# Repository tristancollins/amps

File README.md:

# Amps
## Generic Boards
- General MOSFET breakout
- General TO220 breakout

I've moved my amp pcbs to their own repos.
- Guitar Pre-amp
- Guitar Phase Inverter (LTPI)
- Guitar Valve-driven effects loop
- Guitar Power Supply
- Guitar Bone Ray Tone Stack
- Guitar Solid State effects loop
- Guitar Solid State Reverb
- Guitar Input PCB - UNTESTED - for my specific builds
- Guitar Cathodyne Phase Inverter - UNTESTED

In action: https://www.tristancollins.me/ax84/Mutineer/Built/IMG_0032.jpg
https://www.tristancollins.me/ax84/Mutineer/Built/IMG_0031.jpg

- HiFi PCL82 SE board
- HiFi Maida Regulator
- HiFi 5V supply and mains relay
- HiFi Baxandall Preamp

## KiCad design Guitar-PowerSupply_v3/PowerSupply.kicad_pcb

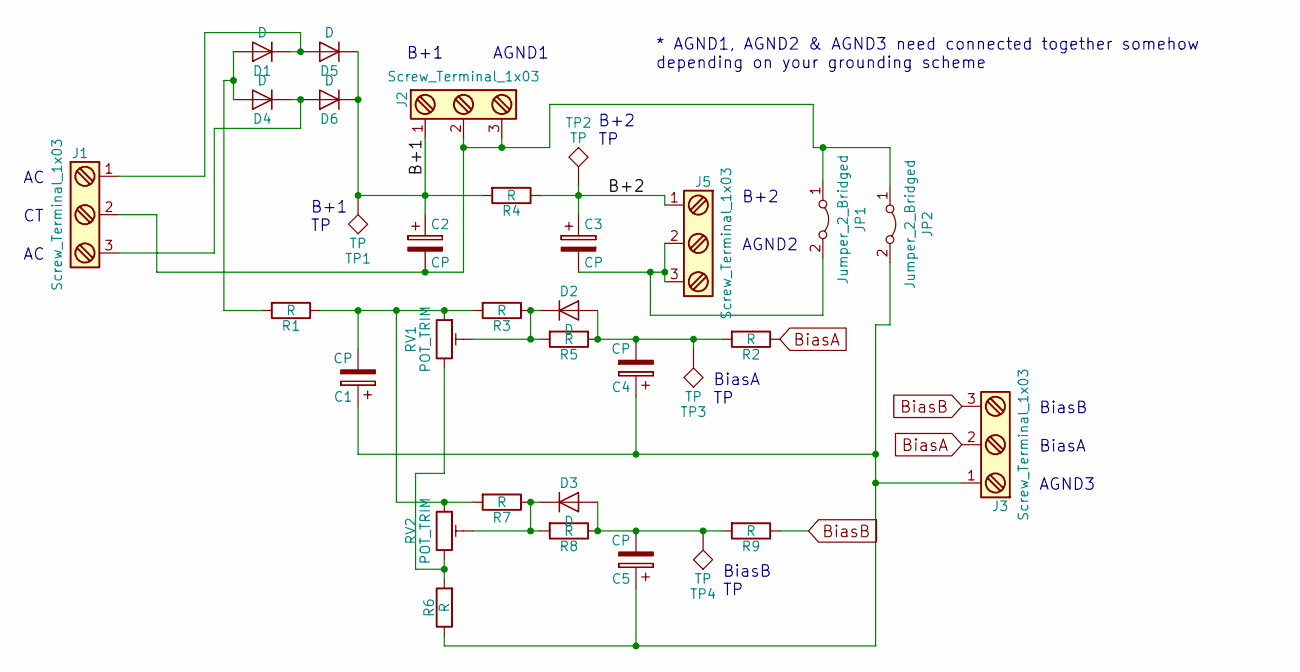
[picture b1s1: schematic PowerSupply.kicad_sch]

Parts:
C1, C4, C5: CP; CP_Radial_D10.0mm_P2.50mm_P5.00mm; MPN UPW2C100MPD
C2, C3: CP; CP_Radial_D18.0mm_P7.50mm
D1, D2, D3, D4, D5, D6: D; Diode_DO-41_SOD81_Horizontal_RM10
J1, J2, J3, J5: Screw_Terminal_1x03; PhoenixContact_MCV-G_03x5.08mm_Vertical; MPN 1729131
JP1, JP2: Jumper_2_Bridged; SolderJumper-2_P1.3mm_Bridged_RoundedPad1.0x1.5mm
R1: R; R_Axial_DIN0516_L15.5mm_D5.0mm_P20.32mm_Horizontal
R2, R3, R5, R6, R7, R8, R9: R; R_Axial_DIN0309_L9.0mm_D3.2mm_P12.70mm_Horizontal
R4: R; R_Axial_Power_L48.0mm_W12.5mm_P55.88mm
RV1, RV2: POT_TRIM; Potentiometer_Trimmer_Bourns_3339S_Vertical; MPN 3386P-1-103TLF
TP1, TP2, TP3, TP4: TP; Test_Point_Keystone_5005-5009_Compact

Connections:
/B+1: C2.1, D5.1 (K), D6.1 (K), J2.1, R4.2, TP1.1
/B+2: C3.1, J5.1, R4.1, TP2.1
BiasA: J3.2, R2.1
BiasB: J3.3, R9.1
unnamed: C1.1, C4.1, C5.1, J3.1, JP2.2 (B), R6.1
unnamed: C1.2, R1.1, R3.2, R7.2, RV1.1, RV2.1
unnamed: C2.2, J1.2, J2.2, J2.3, JP1.1 (A), JP2.1 (A)
unnamed: C3.2, J5.2, J5.3, JP1.2 (B)
unnamed: C4.2, D2.2 (A), R2.2, R5.1, TP3.1
unnamed: C5.2, D3.2 (A), R8.1, R9.2, TP4.1
unnamed: D1.1 (K), D5.2 (A), J1.1
unnamed: D1.2 (A), D4.2 (A), R1.2
unnamed: D2.1 (K), R3.1, R5.2, RV1.2
unnamed: D3.1 (K), R7.1, R8.2, RV2.2
unnamed: D4.1 (K), D6.2 (A), J1.3
unnamed: R6.2, RV1.3, RV2.3

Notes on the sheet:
B+2 TP
B+1 TP
BiasB
BiasA TP
* AGND1, AGND2 & AGND3 need connected together somehow depending on your grounding scheme
AGND2
B+2
BiasB TP
B+1
BiasA
AGND1
AGND3

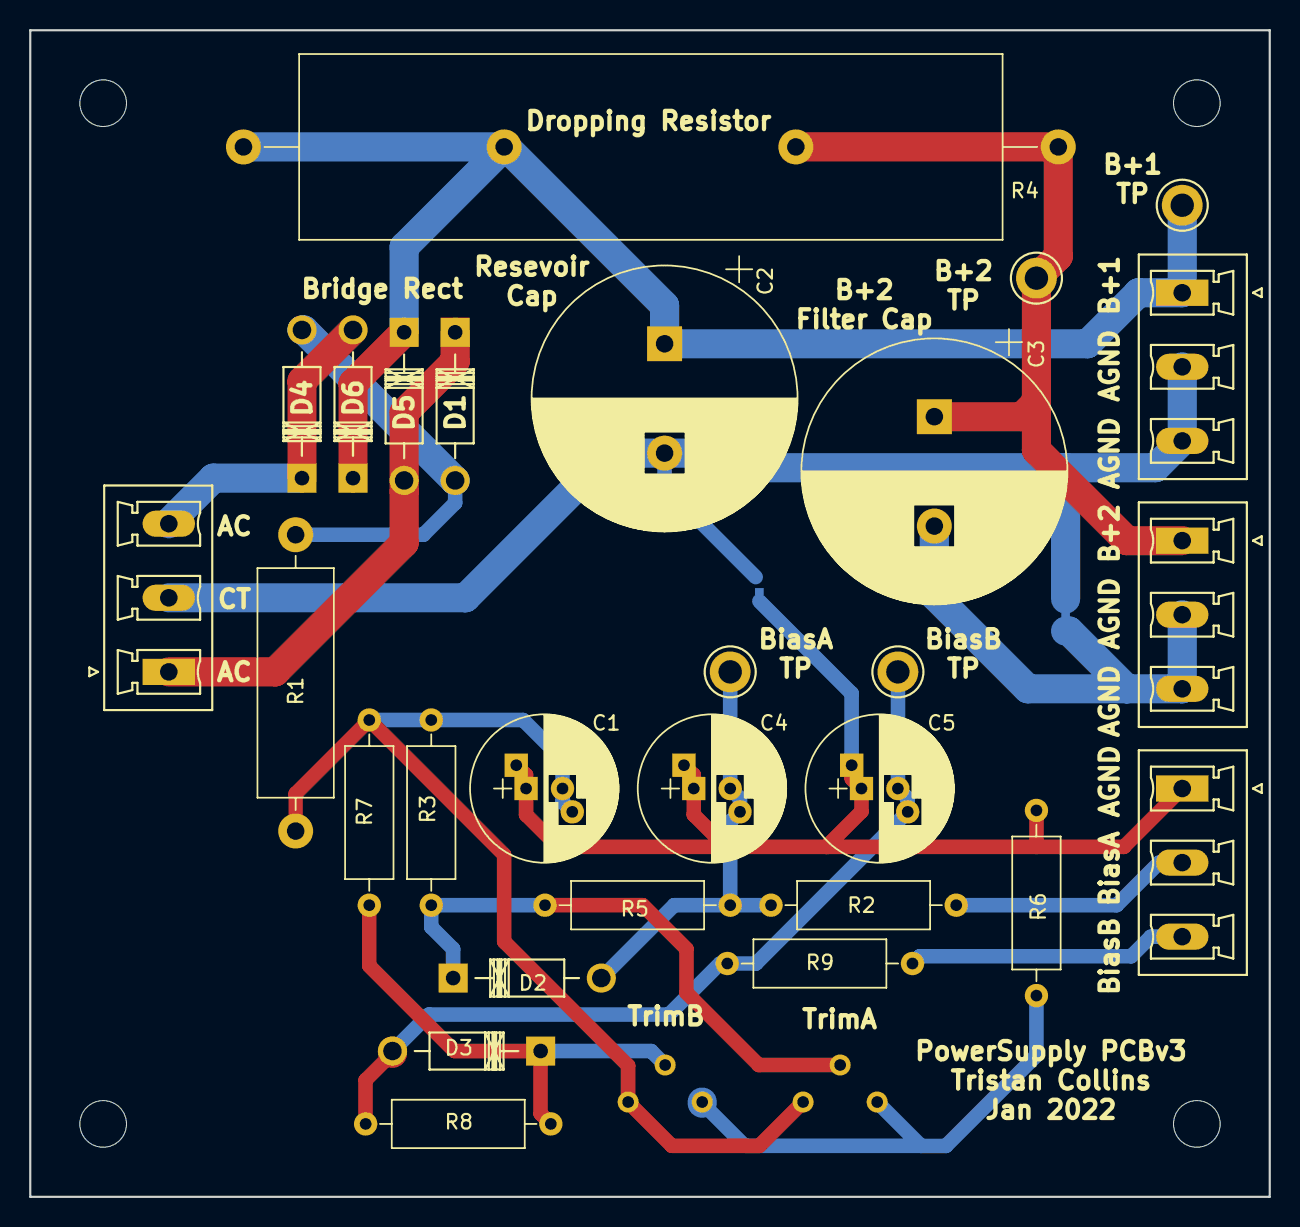
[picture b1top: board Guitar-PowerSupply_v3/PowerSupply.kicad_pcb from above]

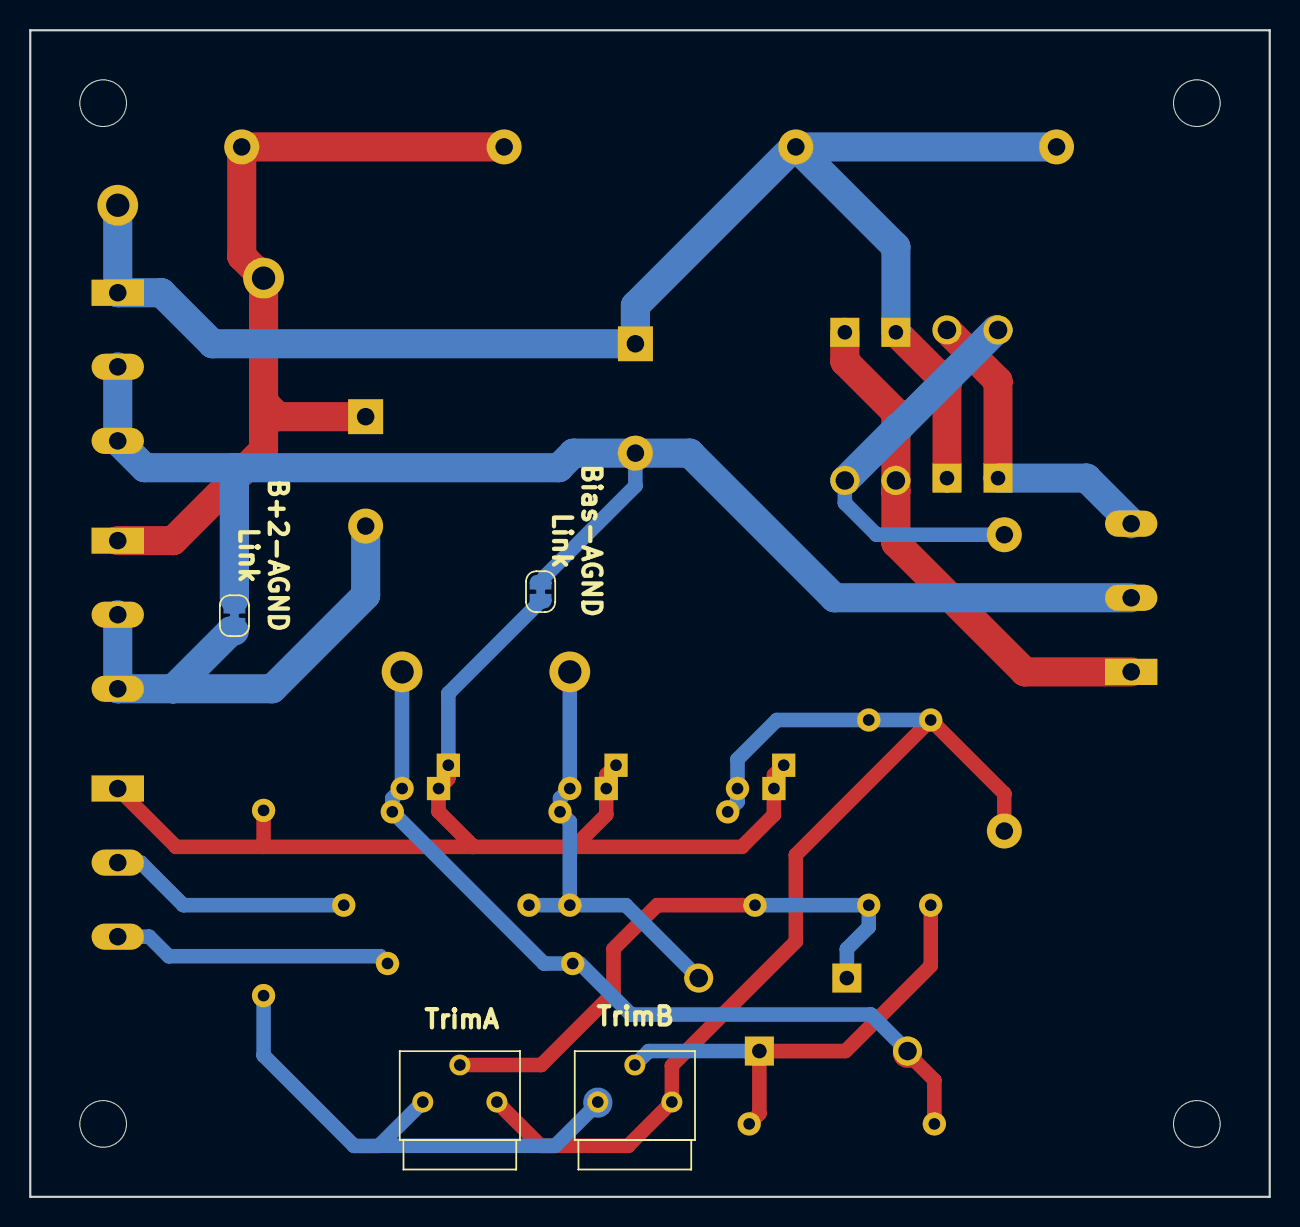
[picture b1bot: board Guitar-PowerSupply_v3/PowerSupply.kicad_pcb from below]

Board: 2 copper layers, 85.0 x 80.0 mm, 32 parts (4 on the bottom side), 16 nets.

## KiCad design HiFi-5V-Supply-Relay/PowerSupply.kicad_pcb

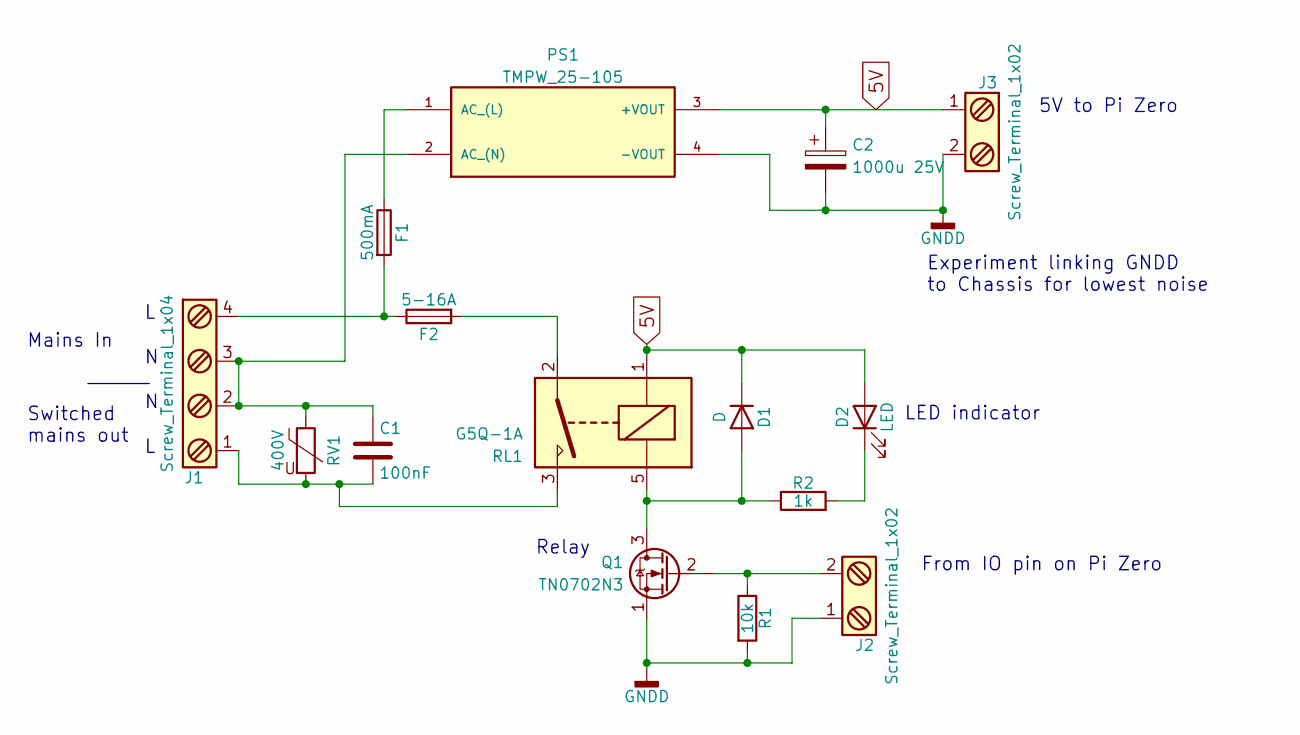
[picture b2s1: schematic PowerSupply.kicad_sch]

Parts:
C1: 100nF; C_Rect_L18.0mm_W5.0mm_P15.00mm_FKS3_FKP3; mpn 80-R71PI3100JE3EK
C2: 1000u 25V; CP_Radial_D10.0mm_P5.00mm
D1: D; D_DO-41_SOD81_P3.81mm_Vertical_KathodeUp
D2: LED; PinHeader_1x02_P2.54mm_Vertical
F1: 500mA; Fuseholder_Cylinder-5x20mm_Bulgin_FX0456_Vertical_Closed; mpn FX0456
F2: 5-16A; Fuseholder_Cylinder-5x20mm_Bulgin_FX0456_Vertical_Closed; mpn FX0456
J1: Screw_Terminal_1x04; TerminalBlock_Phoenix_PT-1,5-4-5.0-H_1x04_P5.00mm_Horizontal
J2, J3: Screw_Terminal_1x02; TerminalBlock_Phoenix_PT-1,5-2-3.5-H_1x02_P3.50mm_Horizontal
PS1: TMPW_25-105; CONV_TMPW_25-105; PARTREV April 20,2021
Q1: TN0702N3; TO-92_HandSolder; mpn TN0702N3-G
R1: 10k; R_Axial_DIN0207_L6.3mm_D2.5mm_P2.54mm_Vertical
R2: 1k; R_Axial_DIN0207_L6.3mm_D2.5mm_P2.54mm_Vertical
RL1: G5Q-1A; Relay_SPST_Omron-G5Q-1A; mpn G5Q-1A4-EU DC5
RV1: 400V; RV_Disc_D7mm_W5.1mm_P5mm; mpn 495-3785-ND

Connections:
5V: C2.1, D1.1 (K), D2.2 (A), J3.1, PS1.3 (+VOUT), RL1.1
GNDD: C2.2, J2.1, J3.2, PS1.4 (-VOUT), Q1.1 (S), R1.2
unnamed: C1.1, J1.2, J1.3, PS1.2 (AC_(N)), RV1.1
unnamed: C1.2, J1.1, RL1.3, RV1.2
unnamed: D1.2 (A), Q1.3 (D), R2.1, RL1.5
unnamed: D2.1 (K), R2.2
unnamed: F1.1, PS1.1 (AC_(L))
unnamed: F1.2, F2.1, J1.4
unnamed: F2.2, RL1.2
unnamed: J2.2, Q1.2 (G), R1.1

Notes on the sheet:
From IO pin on Pi Zero
Mains In
Relay
LED indicator
Switched mains out
Experiment linking GNDD to Chassis for lowest noise
5V to Pi Zero

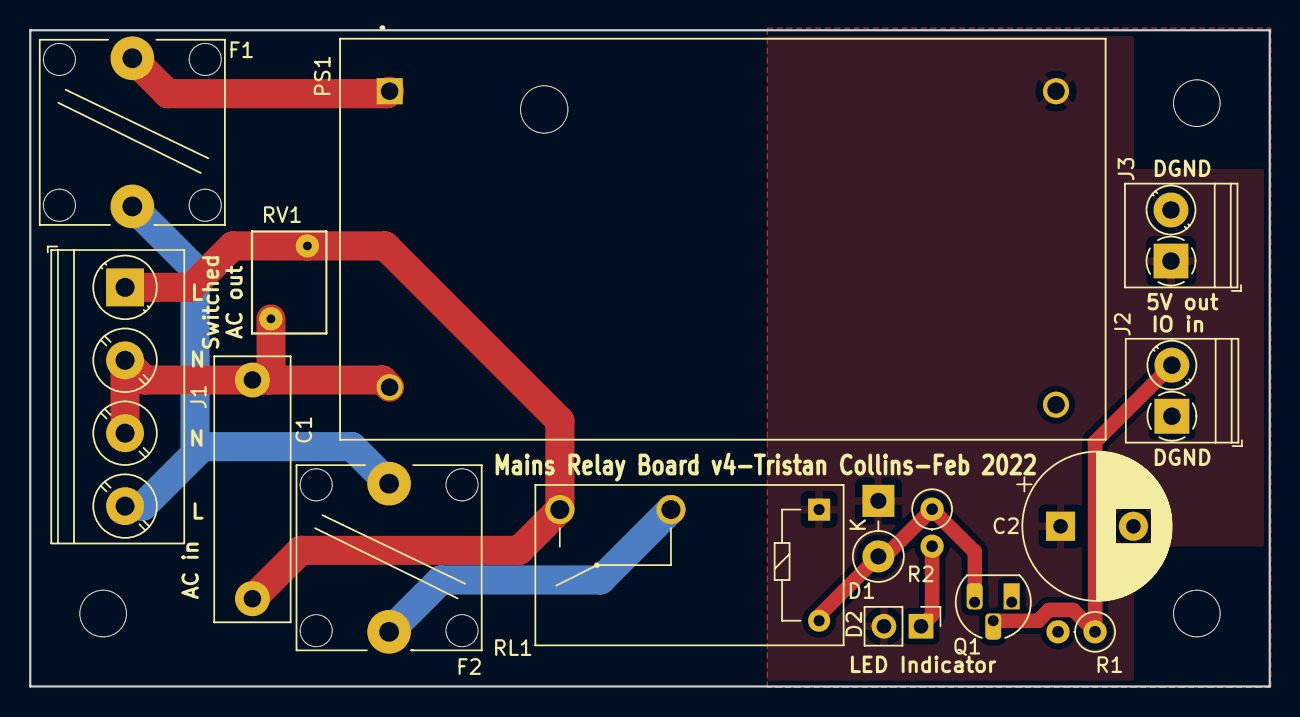
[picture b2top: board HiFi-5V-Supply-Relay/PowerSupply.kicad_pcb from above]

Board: 2 copper layers, 85.0 x 45.0 mm, 15 parts (0 on the bottom side), 10 nets.

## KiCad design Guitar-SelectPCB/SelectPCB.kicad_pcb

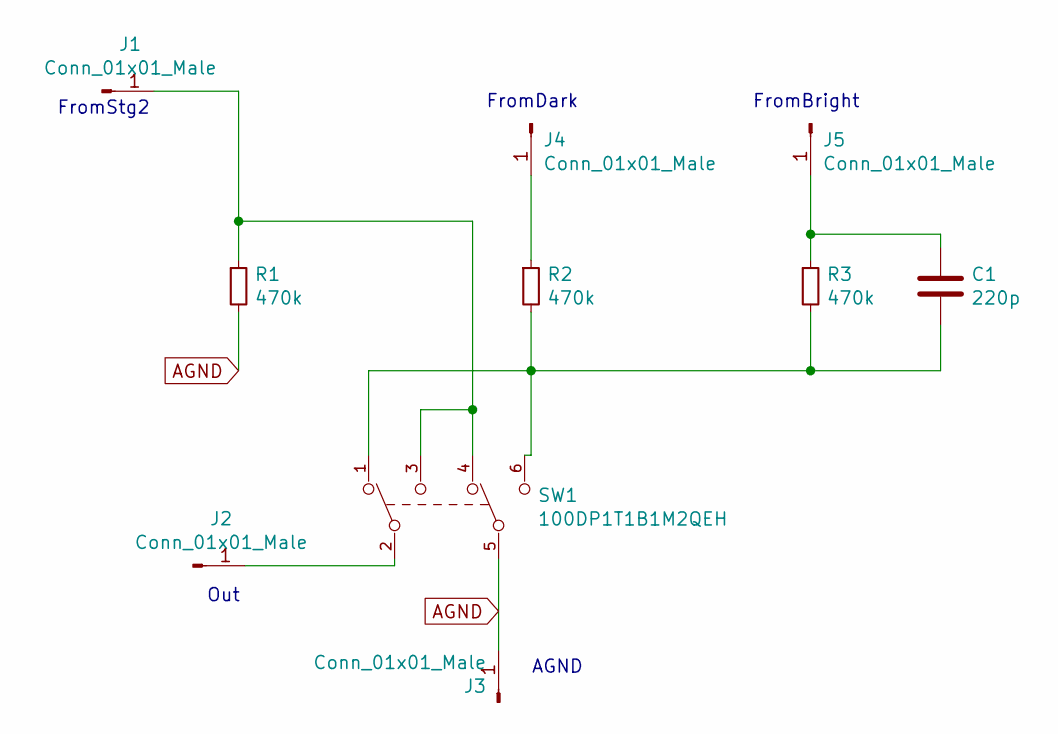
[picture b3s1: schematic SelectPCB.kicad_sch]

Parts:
C1: 220p; C_Disc_D7.5mm_W5.0mm_P7.50mm
J1, J2, J3, J4, J5: Conn_01x01_Male; SolderWirePad_1x01_Drill1.5mm
R1, R2, R3: 470k; R_Axial_DIN0207_L6.3mm_D2.5mm_P10.16mm_Horizontal
SW1: 100DP1T1B1M2QEH; E-Switch-100DP1T1B1M2QEH-0; Current Rating 5A (AC/DC); Voltage Rating - AC 120V; mouser part number 612-100-F1121; digikey description Toggle Switch DPDT Panel Mount

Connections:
AGND: J3.1, R1.2, SW1.5
unnamed: C1.1, J5.1, R3.1
unnamed: C1.2, R2.2, R3.2, SW1.1, SW1.6
unnamed: J1.1, R1.1, SW1.3, SW1.4
unnamed: J2.1, SW1.2
unnamed: J4.1, R2.1

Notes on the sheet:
Out
FromBright
FromDark
AGND
FromStg2

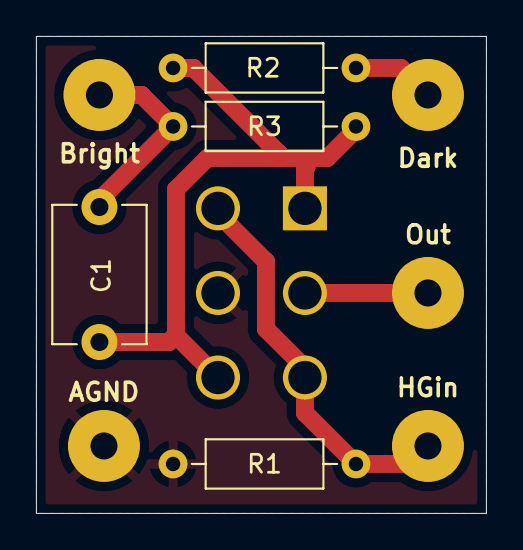
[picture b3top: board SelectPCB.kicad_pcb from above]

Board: 2 copper layers, 25.0 x 26.5 mm, 10 parts (1 on the bottom side), 6 nets.

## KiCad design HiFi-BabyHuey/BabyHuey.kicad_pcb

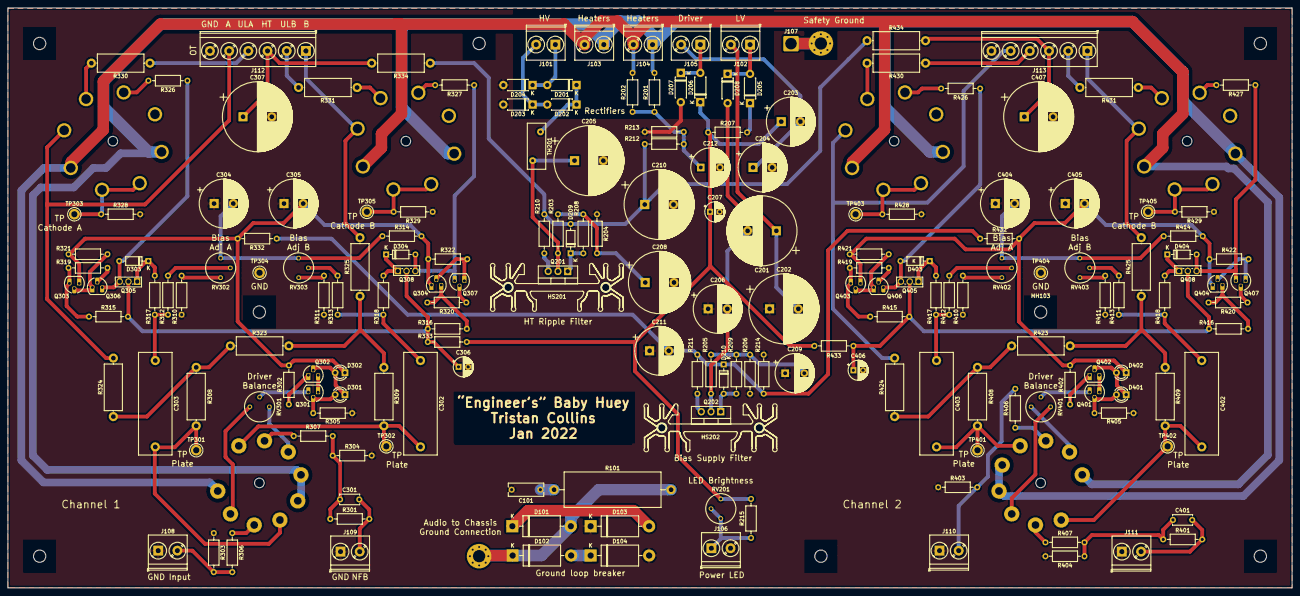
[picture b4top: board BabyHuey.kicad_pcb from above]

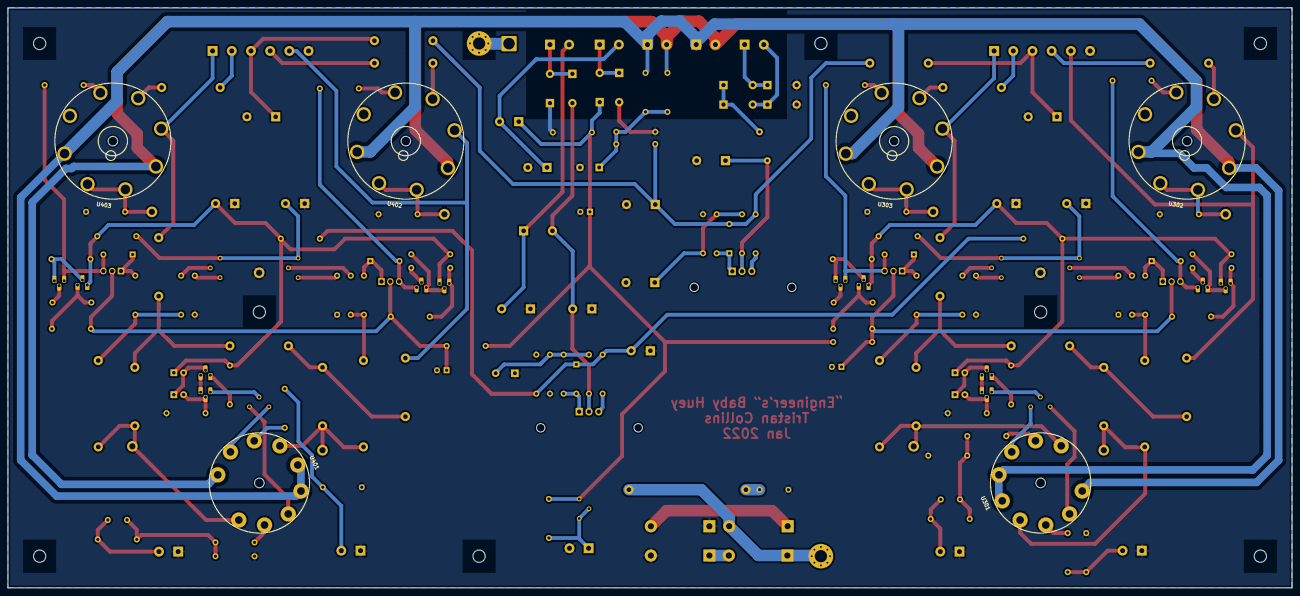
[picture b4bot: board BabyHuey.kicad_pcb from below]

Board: 2 copper layers, 334.5 x 151.1 mm, 200 parts (6 on the bottom side), 120 nets.

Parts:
C101: 100n; C_Rect_L9.0mm_W3.2mm_P7.50mm_MKT
C201, C202: 470u 100V; CP_Radial_D18.0mm_P7.50mm
C203, C204: 2200u 25V; CP_Radial_D12.5mm_P5.00mm
C205, C210, C307, C407: 47u 450V; CP_Radial_D18.0mm_P7.50mm
C206, C211, C304, C305, C404, C405: 47u 160V; CP_Radial_D12.5mm_P5.00mm
C207, C306, C406: 47u 25V; CP_Radial_D5.0mm_P2.50mm
C208: 10u 450V; CP_Radial_D16.0mm_P7.50mm
C209: 10u 160V; CP_Radial_D10.0mm_P5.00mm
C212: 10u 200V; CP_Radial_D10.0mm_P5.00mm
C301, C401: DNP; C_Disc_D5.0mm_W2.5mm_P5.00mm
C302, C303, C402, C403: 220n 630V; C_Rect_L26.5mm_W8.5mm_P22.50mm_MKS4
D101, D102, D103, D104: SF51-B; D_DO-201AD_P15.24mm_Horizontal
D201, D202, D203, D204, D205, D206, D207, D208: UF4007; D_DO-41_SOD81_P7.62mm_Horizontal
D209, D210, D303, D304, D403, D404: BZX79C10; D_DO-35_SOD27_P7.62mm_Horizontal
D301, D302, D401, D402: Red; LED_D3.0mm
HS201, HS202: HSE-B20250-040H
J101, J102, J103, J104, J105, J106, J108, J109, J110, J111: Screw_Terminal_01x02; TerminalBlock_Phoenix_PT-1,5-2-5.0-H_1x02_P5.00mm_Horizontal
J107: Conn_01x01_Female; SolderWire-2.5sqmm_1x01_D2.4mm_OD3.6mm
J112, J113: Screw_Terminal_01x06; TerminalBlock_Phoenix_PT-1,5-6-5.0-H_1x06_P5.00mm_Horizontal
MH101, MH102, MH103, MH104, MH105, MH106, MH107, MH108: MountingHole; MountingHole_3.2mm_M3
MH109, MH110: MountingHole_Pad; MountingHole_3.2mm_M3_Pad_Via
Q201: FQPF8N60C; TO-220-3_Vertical
Q202: FQPF7P20; TO-220-3_Vertical
Q301, Q302, Q303, Q304, Q306, Q307, Q401, Q402, Q403, Q404, Q406, Q407: 2n5551; TO-92_HandSolder
Q305, Q308, Q405, Q408: STU9HN65M2; TO-251-3_Vertical
R101: 10r 5W; R_Axial_Power_L25.0mm_W9.0mm_P30.48mm
R201, R202, R208, R209, R317, R318, R319, R320, R417, R418, R419, R420: 100r; R_Axial_DIN0207_L6.3mm_D2.5mm_P10.16mm_Horizontal
R203, R205, R314, R414: 22k; R_Axial_DIN0207_L6.3mm_D2.5mm_P10.16mm_Horizontal
R204, R206, R312, R313, R412, R413: 1Meg; R_Axial_DIN0207_L6.3mm_D2.5mm_P10.16mm_Horizontal
R207, R212, R214: 330k; R_Axial_DIN0207_L6.3mm_D2.5mm_P10.16mm_Horizontal
R210: 22r; R_Axial_DIN0207_L6.3mm_D2.5mm_P10.16mm_Horizontal
R211: 10r; R_Axial_DIN0207_L6.3mm_D2.5mm_P10.16mm_Horizontal
R213, R305, R405: 47k; R_Axial_DIN0207_L6.3mm_D2.5mm_P10.16mm_Horizontal
R215: TBD; R_Axial_DIN0207_L6.3mm_D2.5mm_P10.16mm_Horizontal
R301, R401: DNP; R_Axial_DIN0207_L6.3mm_D2.5mm_P10.16mm_Horizontal
R302, R402: 680r; R_Axial_DIN0207_L6.3mm_D2.5mm_P10.16mm_Horizontal
R303, R403: 100k; R_Axial_DIN0207_L6.3mm_D2.5mm_P10.16mm_Horizontal
R304, R404: 470r; R_Axial_DIN0207_L6.3mm_D2.5mm_P10.16mm_Horizontal
R306, R307, R310, R311, R326, R327, R406, R407, R410, R411, R426, R427: 1k; R_Axial_DIN0207_L6.3mm_D2.5mm_P10.16mm_Horizontal
R308, R309, R408, R409: 220k 2W; R_Axial_DIN0414_L11.9mm_D4.5mm_P15.24mm_Horizontal
R315, R316, R415, R416: 220k; R_Axial_DIN0207_L6.3mm_D2.5mm_P10.16mm_Horizontal
R321, R322, R421, R422: 390r; R_Axial_DIN0207_L6.3mm_D2.5mm_P10.16mm_Horizontal
R323, R423: 39k 2W; R_Axial_DIN0414_L11.9mm_D4.5mm_P15.24mm_Horizontal
R324, R325, R424, R425: 47k 2W; R_Axial_DIN0414_L11.9mm_D4.5mm_P15.24mm_Horizontal
R328, R329, R428, R429: 10r 1%; R_Axial_DIN0207_L6.3mm_D2.5mm_P10.16mm_Horizontal
R330, R331, R430, R431: 1k 2W; R_Axial_DIN0414_L11.9mm_D4.5mm_P15.24mm_Horizontal
R332, R333, R432, R433: 270r; R_Axial_DIN0207_L6.3mm_D2.5mm_P10.16mm_Horizontal
R334, R434: 10r 2W; R_Axial_DIN0414_L11.9mm_D4.5mm_P15.24mm_Horizontal
RV201, RV302, RV303, RV402, RV403: 50k; Potentiometer_Bourns_3339P_Vertical
RV301, RV401: 470r; Potentiometer_Bourns_3339P_Vertical
TH201: CL140; RV_Disc_D12mm_W4.8mm_P7.5mm
TP301, TP302, TP303, TP304, TP305, TP401, TP402, TP403, TP404, TP405: TestPoint; TestPoint_Keystone_5005-5009_Compact
U301, U401: ECC83; VALVE-ECC-83-1-TC
U302, U303, U402, U403: EL34; Octal

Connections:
/B+: C210.1, D209.2, R210.1, R212.1, R334.1, R434.1
/Left/B+: C307.1, J112.3, R334.2
/Left/B+A: J112.5, R324.2, U302.3
/Left/B+B: J112.1, R325.2, U303.3
/Left/GNFB: C301.2, J109.2, R301.2
/Left/Input: J108.2, R303.2, R306.2
/Left/LTPI: Q301.3, RV301.2
/Left/ULA: J112.4, R330.1
/Left/ULB: J112.2, R331.2
/Left/V_neg: C305.2, D302.1, Q303.1, Q304.1, R302.2, R314.2, R321.2, R322.1, R332.2
/Left/V_pos: C306.1, Q305.2, Q308.2, R315.2, R316.1, R333.2
/PowerSupply/Driver+: D206.2, D207.1, J105.1
/PowerSupply/Driver-: C203.2, C204.1, J105.2
/PowerSupply/HV+: D201.2, D204.1, J101.1
/PowerSupply/HV-: D202.2, D203.1, J101.2
/PowerSupply/LV+: D205.2, D208.1, J102.1
/PowerSupply/LV-: C201.1, C202.2, J102.2
/PowerSupply/PowerLED: J106.1, R215.1, RV201.1, RV201.2
/PowerSupply/V_elevation: C212.1, R201.2, R202.1, R212.2, R213.1
/Right/B+: C407.1, J113.3, R434.2
/Right/B+A: J113.5, R424.2, U402.3
/Right/B+B: J113.1, R425.2, U403.3
/Right/GNFB: C401.2, J111.2, R401.2
/Right/Input: J110.2, R403.2, R406.2
/Right/LTPI: Q401.3, RV401.2
/Right/ULA: J113.4, R430.1
/Right/ULB: J113.2, R431.2
/Right/V_neg: C405.2, D402.1, Q403.1, Q404.1, R402.2, R414.2, R421.2, R422.1, R432.2
/Right/V_pos: C406.1, Q405.2, Q408.2, R415.2, R416.1, R433.2
/V_Bias: C211.2, D210.1, R211.1, R214.1, R332.1, R432.1
/V_Driver: C203.1, C207.1, D206.1, R207.1, R215.2, R333.1, R433.1, RV201.3
GNDA: C101.2, C202.1, C204.2, C205.2, C206.1, C207.2, C208.2, C209.1, C210.2, C211.1, C212.2, C304.1, C305.1, C306.2, C307.2, C404.1, C405.1, C406.2, C407.2, D103.1, D104.2, D203.2, D204.2, D205.1, D207.2, J106.2, J108.1, J109.1, J110.1, J111.1, J112.6, J113.6, R204.2, R206.2, R207.2, R213.2, R214.2, R303.1, R304.2, R305.2, R310.1, R311.2, R328.2, R329.1, R403.1, R404.2, R405.2, R410.1, R411.2, R428.2, R429.1, TP304.1, TP404.1
Heater+: J103.1, J104.1, R201.1, U301.4, U301.5, U302.7, U303.7, U401.4, U401.5, U402.7, U403.7
Heater-: J103.2, J104.2, R202.2, U301.9, U302.2, U303.2, U401.9, U402.2, U403.2
unnamed: C101.1, R101.1
unnamed: C201.2, C206.2, D208.2, Q202.2, R205.1
unnamed: C205.1, Q201.2, R203.1, TH201.1
unnamed: C208.1, R203.2, R204.1, R208.2
unnamed: C209.2, R205.2, R206.1, R209.2
unnamed: C301.1, R301.1, R304.1, R307.2
unnamed: C302.1, R313.2, R318.1
unnamed: C302.2, R309.2, TP302.1, U301.1
unnamed: C303.1, R312.1, R317.1
unnamed: C303.2, R308.1, TP301.1, U301.6
unnamed: C304.2, R314.1, RV302.1, RV303.1
unnamed: C401.1, R401.1, R404.1, R407.2
unnamed: C402.1, R413.2, R418.1
unnamed: C402.2, R409.2, TP402.1, U401.1
unnamed: C403.1, R412.1, R417.1
unnamed: C403.2, R408.1, TP401.1, U401.6
unnamed: C404.2, R414.1, RV402.1, RV403.1
unnamed: D101.1, D103.2
unnamed: D101.2, D102.1, MH109.1, R101.2
unnamed: D102.2, D104.1
unnamed: D201.1, D202.1, TH201.2
unnamed: D209.1, Q201.1, R208.1
unnamed: D210.2, Q202.1, R209.1
unnamed: D301.1, D302.2, Q302.2
unnamed: D301.2, Q301.2, R305.1
unnamed: D303.1, Q305.1, R317.2
unnamed: D303.2, Q305.3, Q306.3, R326.1
unnamed: D304.1, Q308.1, R318.2
unnamed: D304.2, Q307.3, Q308.3, R327.1
unnamed: D401.1, D402.2, Q402.2
unnamed: D401.2, Q401.2, R405.1
unnamed: D403.1, Q405.1, R417.2
unnamed: D403.2, Q405.3, Q406.3, R426.1
unnamed: D404.1, Q408.1, R418.2
unnamed: D404.2, Q407.3, Q408.3, R427.1
unnamed: J107.1, MH110.1
unnamed: Q201.3, R210.2
unnamed: Q202.3, R211.2
unnamed: Q301.1, Q302.3
unnamed: Q302.1, R302.1
unnamed: Q303.2, Q306.1, R321.1
unnamed: Q303.3, R315.1, R319.1
unnamed: Q304.2, Q307.1, R322.2
unnamed: Q304.3, R316.2, R320.2
unnamed: Q306.2, R319.2
unnamed: Q307.2, R320.1
unnamed: Q401.1, Q402.3
unnamed: Q402.1, R402.1
unnamed: Q403.2, Q406.1, R421.1
unnamed: Q403.3, R415.1, R419.1
unnamed: Q404.2, Q407.1, R422.2
unnamed: Q404.3, R416.2, R420.2
unnamed: Q406.2, R419.2
unnamed: Q407.2, R420.1
unnamed: R306.1, U301.7
unnamed: R307.1, U301.2
unnamed: R308.2, R323.1, R324.1
unnamed: R309.1, R323.2, R325.1
unnamed: R310.2, RV302.3
unnamed: R311.1, RV303.3
unnamed: R312.2, RV302.2
unnamed: R313.1, RV303.2
unnamed: R326.2, U302.5
unnamed: R327.2, U303.5
unnamed: R328.1, TP303.1, U302.1, U302.8
unnamed: R329.2, TP305.1, U303.1, U303.8
unnamed: R330.2, U302.4
unnamed: R331.1, U303.4
unnamed: R406.1, U401.7
unnamed: R407.1, U401.2
unnamed: R408.2, R423.1, R424.1
unnamed: R409.1, R423.2, R425.1
unnamed: R410.2, RV402.3
unnamed: R411.1, RV403.3
unnamed: R412.2, RV402.2
unnamed: R413.1, RV403.2
unnamed: R426.2, U402.5
unnamed: R427.2, U403.5
unnamed: R428.1, TP403.1, U402.1, U402.8
unnamed: R429.2, TP405.1, U403.1, U403.8
unnamed: R430.2, U402.4
unnamed: R431.1, U403.4
unnamed: RV301.1, U301.8
unnamed: RV301.3, U301.3
unnamed: RV401.1, U401.8
unnamed: RV401.3, U401.3

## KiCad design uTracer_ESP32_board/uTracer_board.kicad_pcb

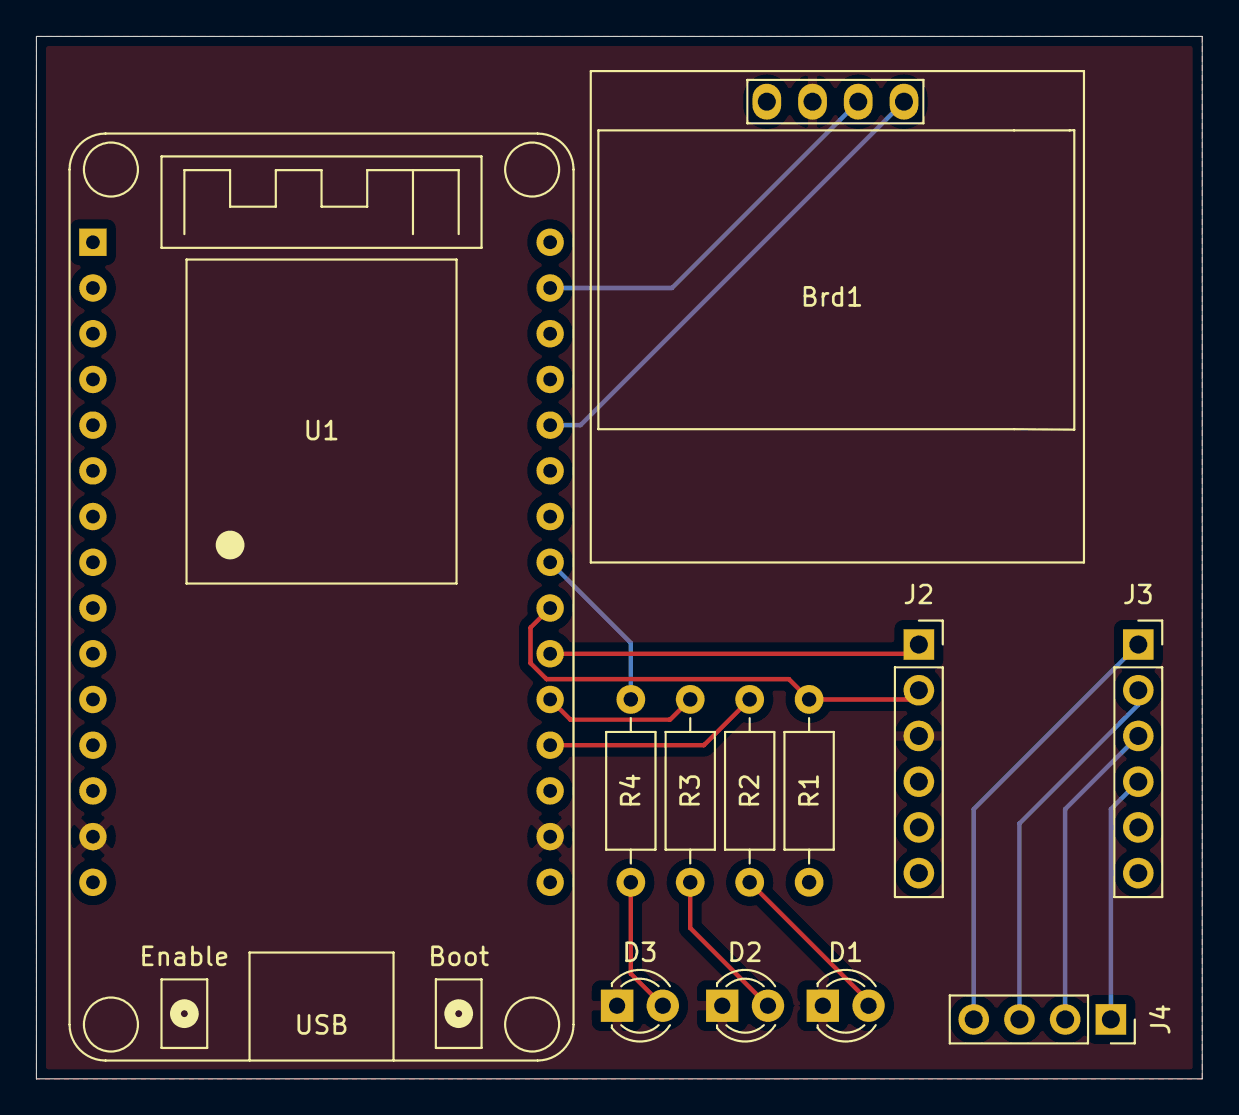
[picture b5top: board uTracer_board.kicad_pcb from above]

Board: 2 copper layers, 64.8 x 57.9 mm, 12 parts (0 on the bottom side), 16 nets.

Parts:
Brd1: SSD1306; 128x64OLED
D1, D2, D3: LED; LED_D3.0mm
J2, J3: Conn_01x06_Female; PinSocket_1x06_P2.54mm_Vertical
J4: Conn_01x04_Female; PinSocket_1x04_P2.54mm_Vertical
R1, R2, R3, R4: R; R_Axial_DIN0207_L6.3mm_D2.5mm_P10.16mm_Horizontal
U1: ESP32_DevKit_V1_DOIT; esp32_devkit_v1_doit

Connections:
+3V3: Brd1.1, J2.4, R1.2, U1.16
/RX: J2.1, U1.21
/TX: J2.2, R1.1, U1.22
GND: Brd1.2, D1.1, D2.1, D3.1, J2.3, U1.14, U1.17
unnamed: Brd1.3, U1.29
unnamed: Brd1.4, U1.26
unnamed: D1.2, R2.2
unnamed: D2.2, R3.2
unnamed: D3.2, R4.2
unnamed: J3.1, J4.4
unnamed: J3.2, J4.3
unnamed: J3.3, J4.2
unnamed: J3.4, J4.1
unnamed: R2.1, U1.19
unnamed: R3.1, U1.20
unnamed: R4.1, U1.23

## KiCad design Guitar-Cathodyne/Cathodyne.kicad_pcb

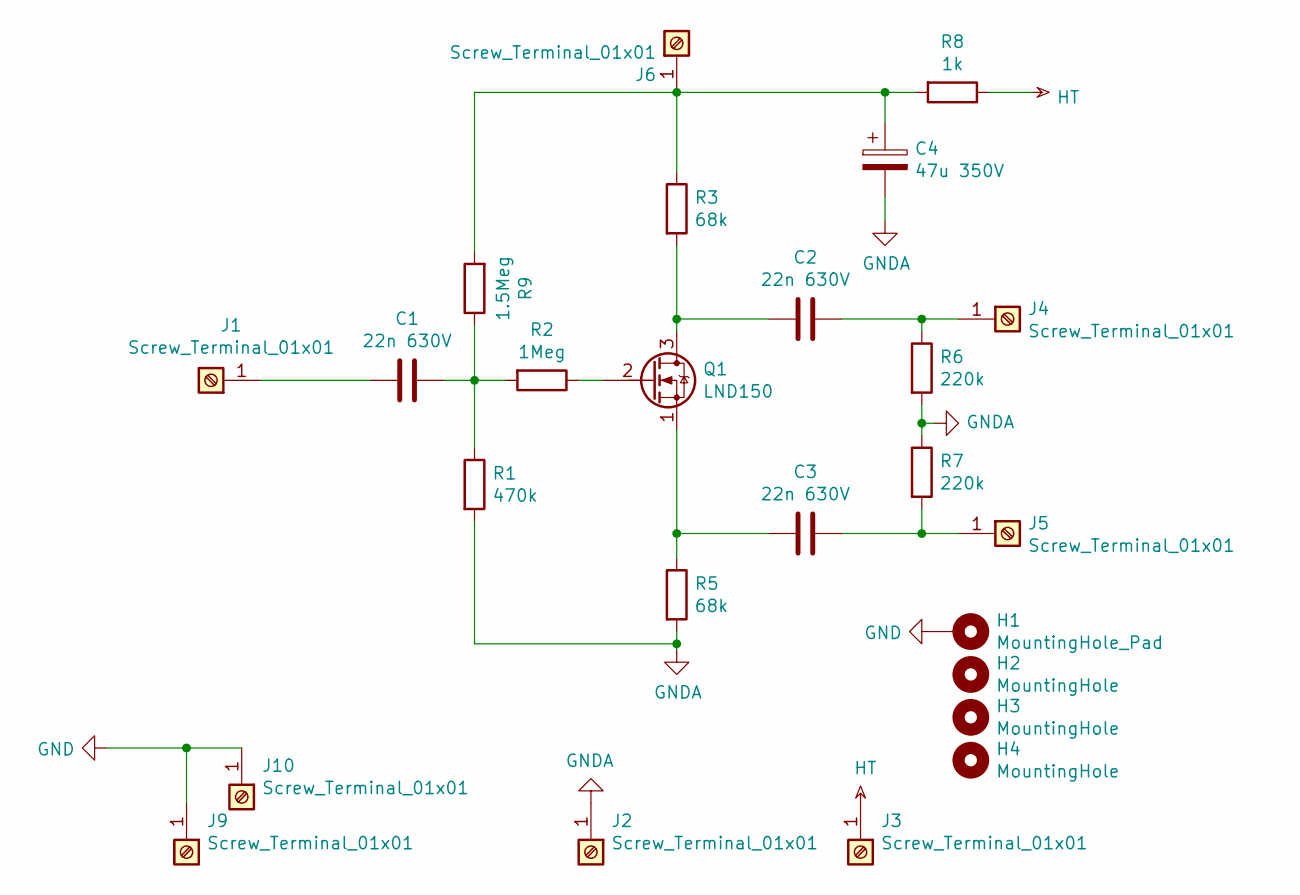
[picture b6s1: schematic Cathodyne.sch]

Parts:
C1, C2, C3: 22n 630V; C_Rect_L13.0mm_W6.5mm_P7.50mm_P10.00mm
C4: 47u 350V; CP_Radial_D12.5mm_P5.00mm
H1: MountingHole_Pad; MountingHole_3.2mm_M3_Pad_Via
H2, H3, H4: MountingHole; MountingHole_3.2mm_M3
J1, J2, J3, J4, J5, J6, J9, J10: Screw_Terminal_01x01; SolderWirePad_1x01_Drill0.8mm
Q1: LND150; TO-92_HandSolder
R1: 470k; R_Axial_DIN0207_L6.3mm_D2.5mm_P7.62mm_Horizontal
R2: 1Meg; R_Axial_DIN0207_L6.3mm_D2.5mm_P7.62mm_Horizontal
R3, R5: 68k; R_Axial_DIN0207_L6.3mm_D2.5mm_P7.62mm_Horizontal
R6, R7: 220k; R_Axial_DIN0207_L6.3mm_D2.5mm_P7.62mm_Horizontal
R8: 1k; R_Axial_DIN0309_L9.0mm_D3.2mm_P12.70mm_Horizontal
R9: 1.5Meg; R_Axial_DIN0207_L6.3mm_D2.5mm_P7.62mm_Horizontal

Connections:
GND: H1.1, J9.1, J10.1
GNDA: C4.2, J2.1, R1.2, R5.2, R6.2, R7.1
HT: J3.1, R8.1
unnamed: C1.1, R1.1, R2.2, R9.1
unnamed: C1.2, J1.1
unnamed: C2.1, J4.1, R6.1
unnamed: C2.2, Q1.3 (D), R3.2
unnamed: C3.1, J5.1, R7.2
unnamed: C3.2, Q1.1 (S), R5.1
unnamed: C4.1, J6.1, R3.1, R8.2, R9.2
unnamed: Q1.2 (G), R2.1

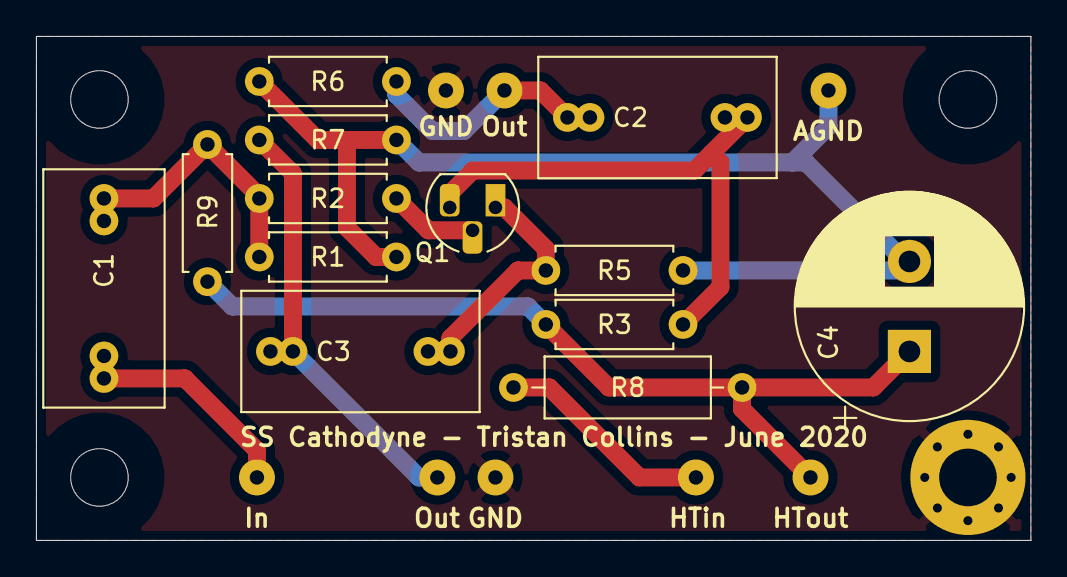
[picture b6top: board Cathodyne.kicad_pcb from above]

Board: 2 copper layers, 55.2 x 28.0 mm, 25 parts (0 on the bottom side), 11 nets.

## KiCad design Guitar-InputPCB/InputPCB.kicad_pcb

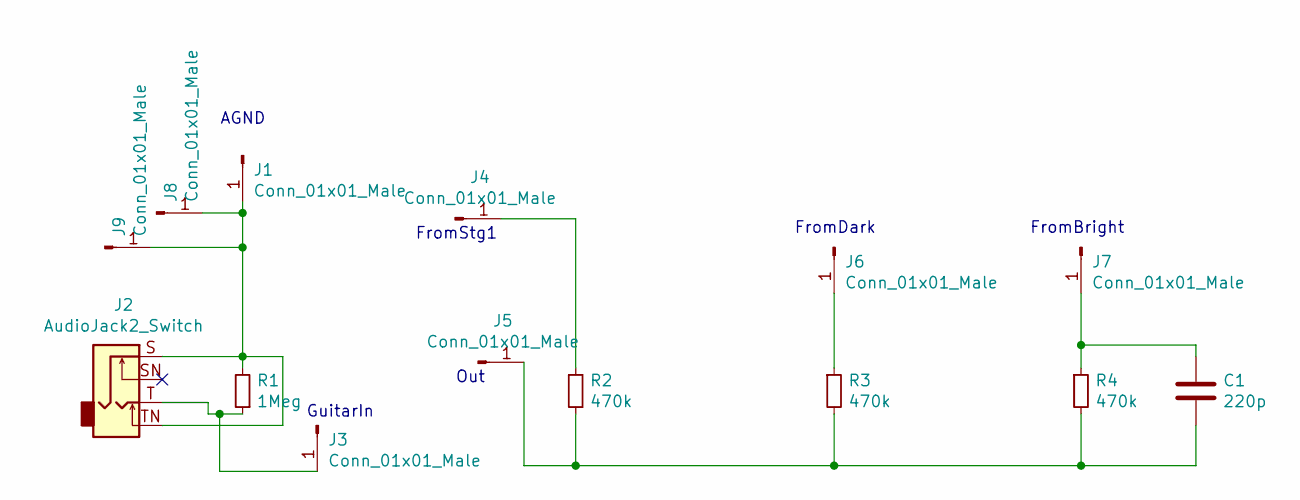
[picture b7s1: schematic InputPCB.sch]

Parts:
C1: 220p; C_Disc_D7.5mm_W2.5mm_P5.00mm
J1, J3, J4, J5, J6, J7, J8, J9: Conn_01x01_Male; SolderWirePad_1x01_Drill0.8mm
J2: AudioJack2_Switch; GuitarJack
R1: 1Meg; R_Axial_DIN0207_L6.3mm_D2.5mm_P7.62mm_Horizontal
R2, R3, R4: 470k; R_Axial_DIN0207_L6.3mm_D2.5mm_P7.62mm_Horizontal

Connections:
unnamed: C1.1, J7.1, R4.1
unnamed: C1.2, J5.1, R2.2, R3.2, R4.2
unnamed: J1.1, J2.S, J2.TN, J8.1, J9.1, R1.2
unnamed: J2.T, J3.1, R1.1
unnamed: J4.1, R2.1
unnamed: J6.1, R3.1

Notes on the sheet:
AGND
GuitarIn
FromStg1
Out
FromDark
FromBright

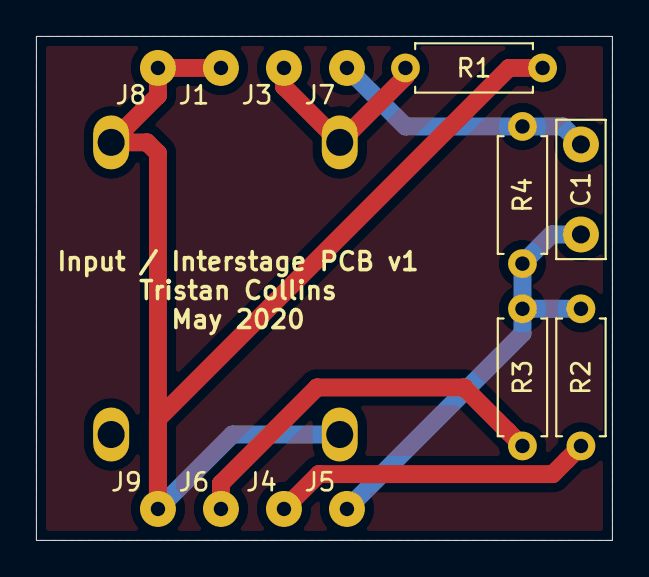
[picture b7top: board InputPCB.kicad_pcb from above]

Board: 2 copper layers, 32.0 x 28.0 mm, 14 parts (1 on the bottom side), 6 nets.
